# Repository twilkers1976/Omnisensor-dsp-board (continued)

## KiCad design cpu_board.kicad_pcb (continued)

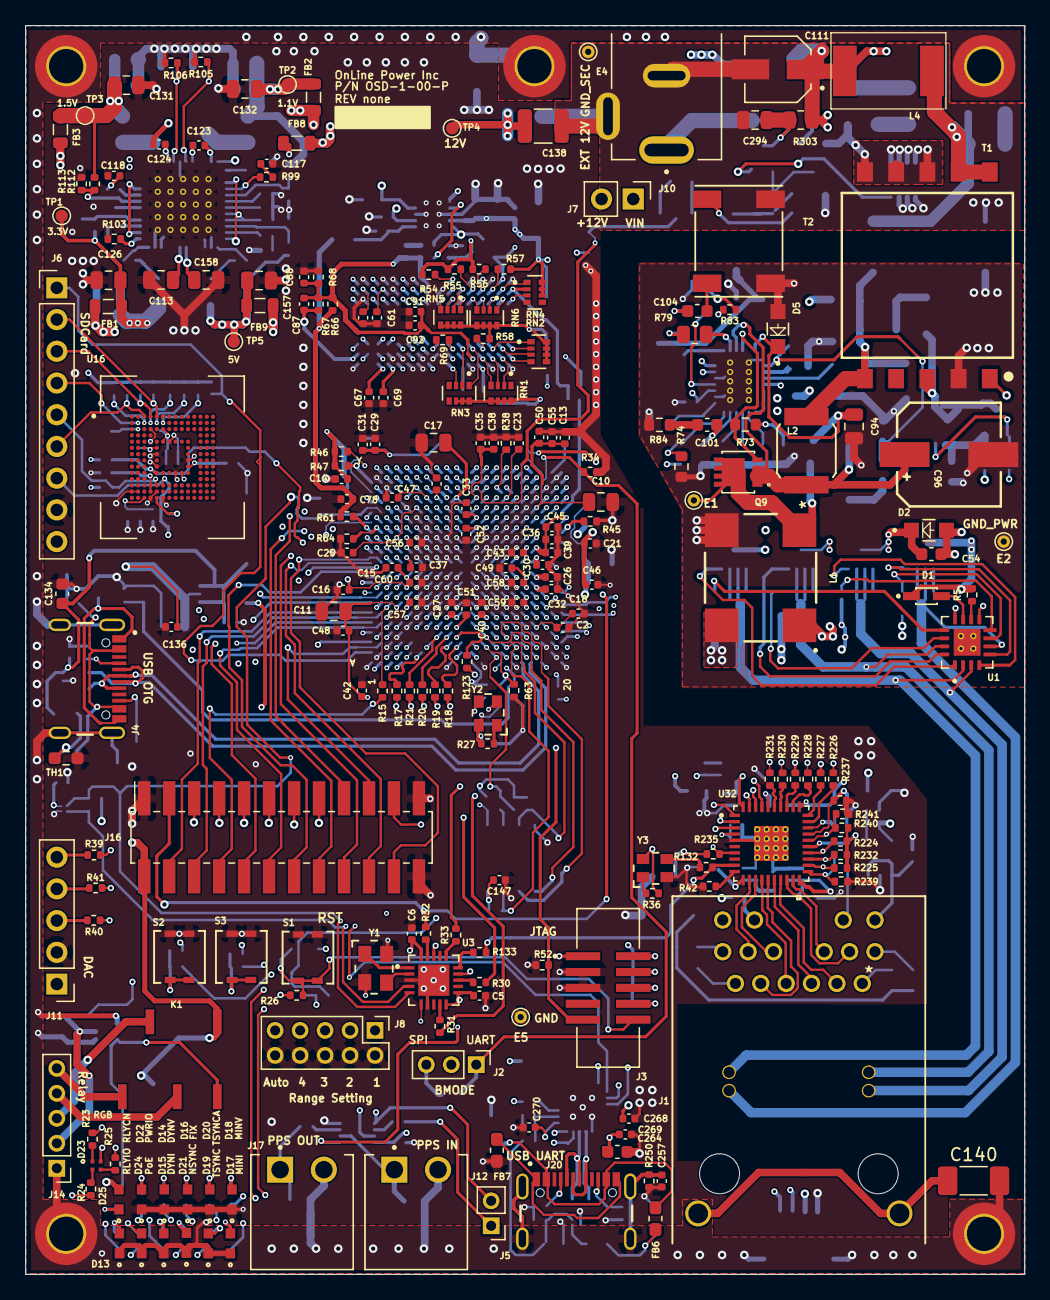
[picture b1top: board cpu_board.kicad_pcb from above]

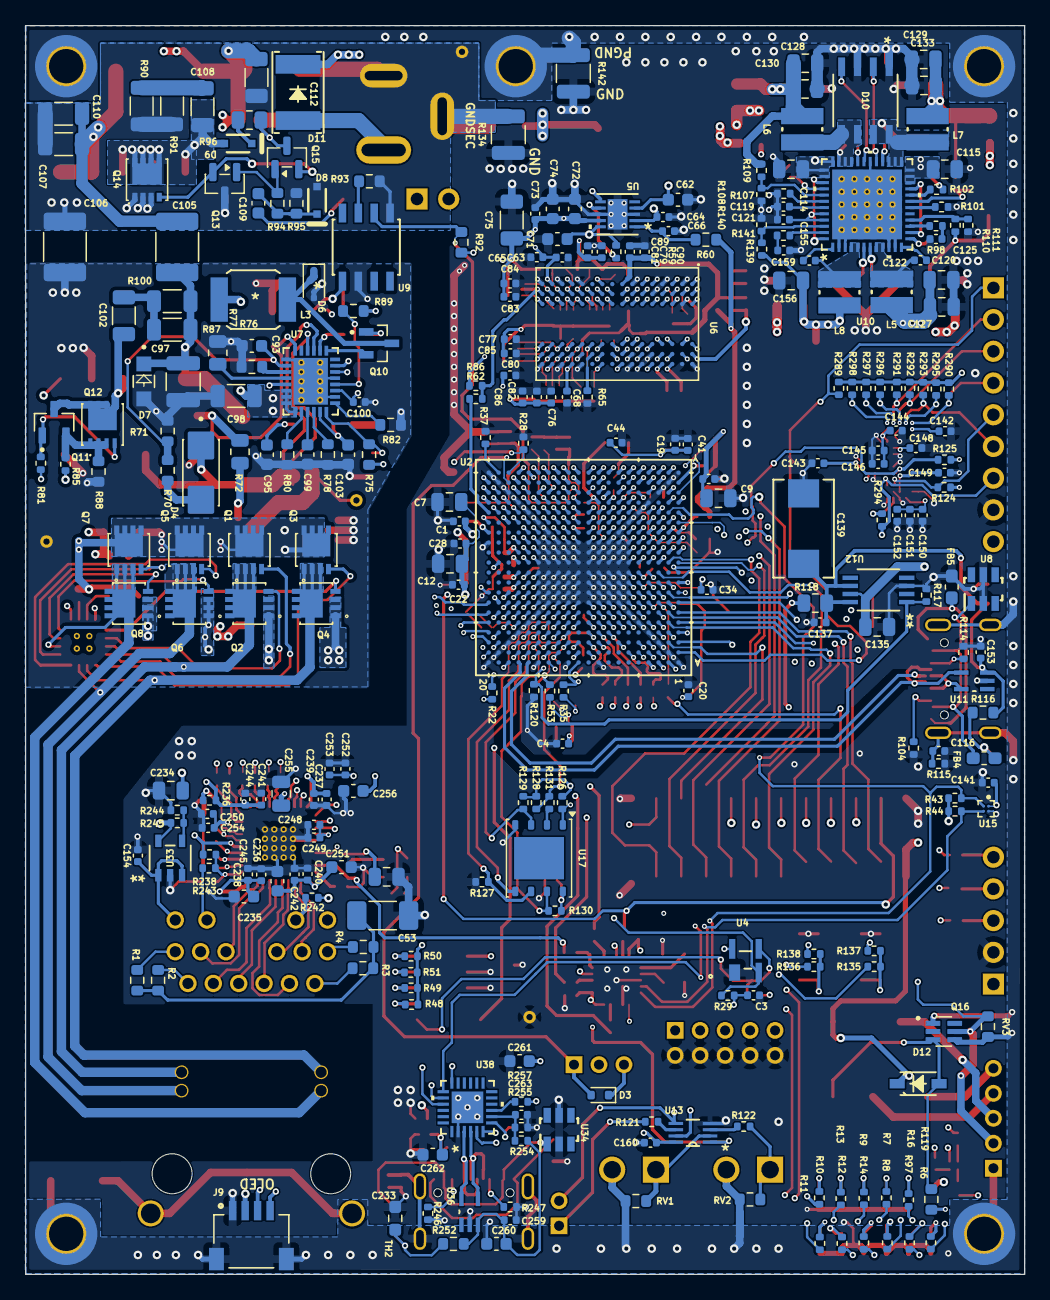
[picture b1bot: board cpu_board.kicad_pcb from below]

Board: 10 copper layers, 80.0 x 100.0 mm, 501 parts (276 on the bottom side), 367 nets.

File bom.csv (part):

"Qty","Reference","Value","Part Number","Manufacturer","Rating","Footprint","Datasheet","DNP"
"72","C1,C2,C3,C4,C5,C6,C13,C14,C15,C16,C17,C18,C19,C20,C21,C22,C23,C24,C25,C26,C27,C28,C29,C30,C31,C32,C33,C34,C37,C40,C61,C63,C65,C66,C67,C68,C69,C70,C87,C88,C89,C91,C122,C123,C124,C141,C143,C144,C145,C146,C147,C148,C149,C150,C151,C152,C153,C154,C155,C160,C237,C238,C241,C242,C248,C250,C253,C259,C263,C268,C269,C270","0.1uf","04025C104KAT2A ","Kyocera AVX","50V","Capacitor_SMD:C_0402_1005Metric","~",""
"11","C7,C8,C9,C10,C11,C12,C113,C114,C115,C135,C158","10uf","EMK212BJ106KG-T","Taiyo Yuden","16V","Capacitor_SMD:C_0805_2012Metric","https://mm.digikey.com/Volume0/opasdata/d220001/medias/docus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",""
"43","C35,C36,C38,C39,C41,C42,C43,C44,C45,C46,C47,C48,C49,C50,C51,C52,C55,C56,C57,C58,C59,C60,C76,C77,C79,C80,C81,C82,C83,C84,C85,C86,C90,C92,C116,C239,C240,C244,C245,C249,C252,C254,C257","0.01uf","04025C103KAT2A","Kyocera AVX","50V","Capacitor_SMD:C_0402_1005Metric","~",""
"2","C53,C140","1000pf","CHV1808N3K0102MXT","Samsung Electro-Mechanics","3KV","Capacitor_SMD:C_1808_4520Metric","https://mm.digikey.com/Volume0/opasdata/d220001/medias/docus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",""
"1","C54","0.047uf","CL10B473KO8NNNC","Samsung Electro-Mechanics","16V","Capacitor_SMD:C_0603_1608Metric","https://mm.digikey.com/Volume0/opasdata/d220001/medias/docus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",""
"3","C62,C71,C74","10uf","GRM188R61C106MAALD","Murata","16V","Capacitor_SMD:C_0603_1608Metric","~",""
"6","C64,C119,C121,C136,C137,C142","1.0uf","EMK105BJ105KV-F","Taiyo Yuden","16V","Capacitor_SMD:C_0402_1005Metric","https://mm.digikey.com/Volume0/opasdata/d220001/medias/docus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",""
"1","C72","22uf","C1608X5R0J226M080AC","Murata","6.3V","Capacitor_SMD:C_0603_1608Metric","~",""
"1","C73","4.7uf","JMK105BBJ475MV-F","Taiyo Yuden","6.3V","Capacitor_SMD:C_0402_1005Metric","~",""
"1","C75","220uf","GMC31X5R227M6R3NT","Cal-chip","6.3V","Capacitor_SMD:C_1206_3216Metric","~",""
"1","C78","100pf","KGM05AR71H101KH","Kyocera AVX","50V","Capacitor_SMD:C_0402_1005Metric","~",""
"1","C93","100pf","CHV0603N250101FCT","Cal Chip","250V","Capacitor_SMD:C_0603_1608Metric","https://calchip.com/wp-content/uploads/2026/01/CHV-Series.pdf",""
"1","C94","0.047uf","C0805C473F4GACTU","Kemet","16V","Capacitor_SMD:C_0805_2012Metric","https://mm.digikey.com/Volume0/opasdata/d220001/medias/docus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",""
"1","C95","0.01uf","KGM15AR71C103KT","Kyocera AVX","16V","Capacitor_SMD:C_0603_1608Metric","https://mm.digikey.com/Volume0/opasdata/d220001/medias/docus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",""
"1","C96","10uf","PCV2A100MCL1GS","Nichicon","100V","omnisensor:PNSC-FT-V-83x83-2_V","https://www.nichicon.co.jp/english/series_items/catalog_pdf/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",""
"1","C97","2.2uf","GRM32ER72A225KA35L","Murata","100V","Capacitor_SMD:C_1210_3225Metric","https://datasheets.kyocera-avx.com/KGM_X7R.pdf",""
"2","C98,C107","10uf","C1206C106M4RACAUTO","KEMET","16V","Capacitor_SMD:C_1206_3216Metric","https://datasheets.kyocera-avx.com/KGM_X7R.pdf,https://mm.digikey.com/Volume0/opasdata/d220001/medias/docus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",""
"1","C99","0.1uf","KGM15BR71H104KT","Kyocera AVX","50V","Capacitor_SMD:C_0603_1608Metric","https://calchip.com/wp-content/uploads/2026/01/CHV-Series.pdf",""
"5","C100,C105,R82,R96,R100","DNP-OPT","","Vishay Dale","1/4 W,2KV","Capacitor_SMD:C_0402_1005Metric,Capacitor_SMD:C_1812_4532Metric,Resistor_SMD:R_0603_1608Metric,Resistor_SMD:R_0805_2012Metric,Resistor_SMD:R_1206_3216Metric","https://www.vishay.com/docs/20035/dcrcwe3.pdf","DNP"
"1","C101","3.3nf","C0603C332J4GACTU","Kemet","16V","Capacitor_SMD:C_0603_1608Metric","https://calchip.com/wp-content/uploads/2026/01/CHV-Series.pdf",""
"1","C102","47pf","CHV1206N1K0470FCT","Cal Chip","1KV","Capacitor_SMD:C_1206_3216Metric","https://calchip.com/wp-content/uploads/2026/04/GMC-Series-1.pdf",""
"1","C103","220pf","CHV0603N250221GCT","Cal Chip","250V","Capacitor_SMD:C_0603_1608Metric","https://calchip.com/wp-content/uploads/2026/01/CHV-Series.pdf",""
"5","C104,C235,C236,C251,C256","1uf","06035C105KAT2A","Kyocera AVX","50V","Capacitor_SMD:C_0603_1608Metric","",""
"1","C106","4.7nf","885012210005","Wurth Elektronik","25V","Capacitor_SMD:C_1812_4532Metric","https://www.we-online.com/components/products/datasheet/8850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",""
"1","C108","470pf","GRM31A7U2J471JW31D","Murata","600V","Capacitor_SMD:C_1206_3216Metric","https://calchip.com/wp-content/uploads/2026/04/GMC-Series-1.pdf",""
"1","C109","2.2nf","GRM188R72A222KA01D","Murata","25V","Capacitor_SMD:C_0603_1608Metric","https://www.we-online.com/components/products/datasheet/8850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",""
"2","C110,C112","DNP-OPT","C1206C106M4RACAUTO","KEMET","16V","Capacitor_SMD:C_1206_3216Metric","https://datasheets.kyocera-avx.com/KGM_X7R.pdf","DNP"
"1","C111","22uf","16SVP22M","Panasonic","16V","omnisensor:CAP_16SVP22M","https://industrial.panasonic.com/ww/products/pt/os-con/model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",""
"2","C117,C118","4700pf","GCM155R71H472KA37D ","Murata","50V","Capacitor_SMD:C_0402_1005Metric","~",""
"1","C120","3000pf","GMC04X7R302K50NT","Murata","50V","Capacitor_SMD:C_0402_1005Metric","~",""
"11","C125,C126,C127,C128,C129,C130,C131,C132,C133,C156,C157","47uf","JMK212BJ476MG-T ","Taiyo Yuden","6.3V","Capacitor_SMD:C_0805_2012Metric","~",""
"5","C134,C260,C261,C262,C264","4.7uf","CL10A475MA8NQNC","Kyocera","25V","Capacitor_SMD:C_0603_1608Metric","~",""
"1","C138","4.7uf","C1210C475K3RACTU","Kemet","25V","Capacitor_SMD:C_1210_3225Metric","https://mm.digikey.com/Volume0/opasdata/d220001/medias/docus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",""
"1","C139","120uf","A700X127M010ATE010","KEMET","10V","omnisensor:CAP_X-7343-43_KEM","https://yageogroup.com/content/datasheet/asset/file/KEM_T209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",""
"1","C159","12nf","GCM155R71H122KA37D","Murata","50V","Capacitor_SMD:C_0402_1005Metric","~",""
"3","C233,C234,C255","4.7uf","CL21A475KBQNNNE","Murata","50V","Capacitor_SMD:C_0805_2012Metric","",""
"1","C294","1uf","CL21B105KOFVPNE","Samsung","16V","Capacitor_SMD:C_0805_2012Metric","https://mm.digikey.com/Volume0/opasdata/d220001/medias/docus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",""
"1","D1","DDZ9709S-7","DDZ9709S-7","Diodes Incorporated","24V","omnisensor:DDZ9709S-7","",""
"3","D2,D5,D7","PTVS58VS1UR,115","PTVS58VS1UR,115","Nexperia","","omnisensor:TVS_PTVS58VS1UR","https://assets.nexperia.com/documents/data-sheet/PTVSXS1UR_SER.pdf",""
"1","D3","1SS389,L3F","1SS389,L3F","Comchip","","Diode_SMD:D_SOD-523","https://www.digikey.com/en/products/detail/comchip-technolog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",""
"1","D4","B2100-13-F","B2100-13-F","Diodes Inc","","omnisensor:DIOM5336X250N","https://www.diodes.com/part/view/B2100",""
"1","D6","BAV19WS","BAV19WS","Diotec","","Diode_SMD:D_SOD-323F","https://diotec.com/request/datasheet/bav19ws.pdf",""
"1","D8","BAT46WJ_115","BAT46WJ,115","Nexperia","","omnisensor:SOD323_V","https://assets.nexperia.com/documents/data-sheet/BAT46WJ.pdf",""
"1","D9","DNP-OPT","BAT46WJ_115","Nexperia","","omnisensor:SOD323_V","https://assets.nexperia.com/documents/data-sheet/BAT46WJ.pdf","DNP"
"1","D10","SI4204DY-T1-GE3","SI4204DY-T1-GE3","Vishay Siliconix","","omnisensor:SOIC8_MS-012_VIS","https://www.vishay.com/docs/65154/si4204dy.pdf",""
"1","D11","CDBA340-G","CDBA340-G","ComChip","","omnisensor:CDBA-G","https://mm.digikey.com/Volume0/opasdata/d220001/medias/docus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",""
"1","D12","MBR0540T1G","MBR0540T1G","onsemi","","omnisensor:SOD-123","https://www.onsemi.com/pdf/datasheet/mbr0540t1-d.pdf",""
"4","D13,D16,D21,D25","Red","B1911USD-20D000114U1930","Harvatek","","omnisensor:LED_B1931NG_HVK","B1931NG--20D001114U1930",""
"5","D14,D17,D18,D19,D22","Green","B1931NG--20D001114U1930","Harvatek","","omnisensor:LED_B1931NG_HVK","B1931NG--20D001114U1930",""
"2","D15,D20","Yellow","KY EELP41.22 Q2T1-36-A8J8-020-R18","OSRAM","","omnisensor:LED_B1931NG_HVK","B1931NG--20D001114U1930",""
"1","D23","RGB LED","UHD111A-FKA-C3K23E1L3VG5ZB3Z3","Cree LED","","omnisensor:SMD4_UHD111A-FKA_CRW","UHD111A-FKA-C3K23E1L3VG5ZB3Z3",""
"1","D24","Blue","B19Y1NB--20C000113U1930","Harvatek","","omnisensor:LED_B1931NG_HVK","B1931NG--20D001114U1930",""
"1","E1","AUX+","MILLMAX 2501-2","","","TestPoint:TestPoint_THTPad_D1.0mm_Drill0.5mm","",""
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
